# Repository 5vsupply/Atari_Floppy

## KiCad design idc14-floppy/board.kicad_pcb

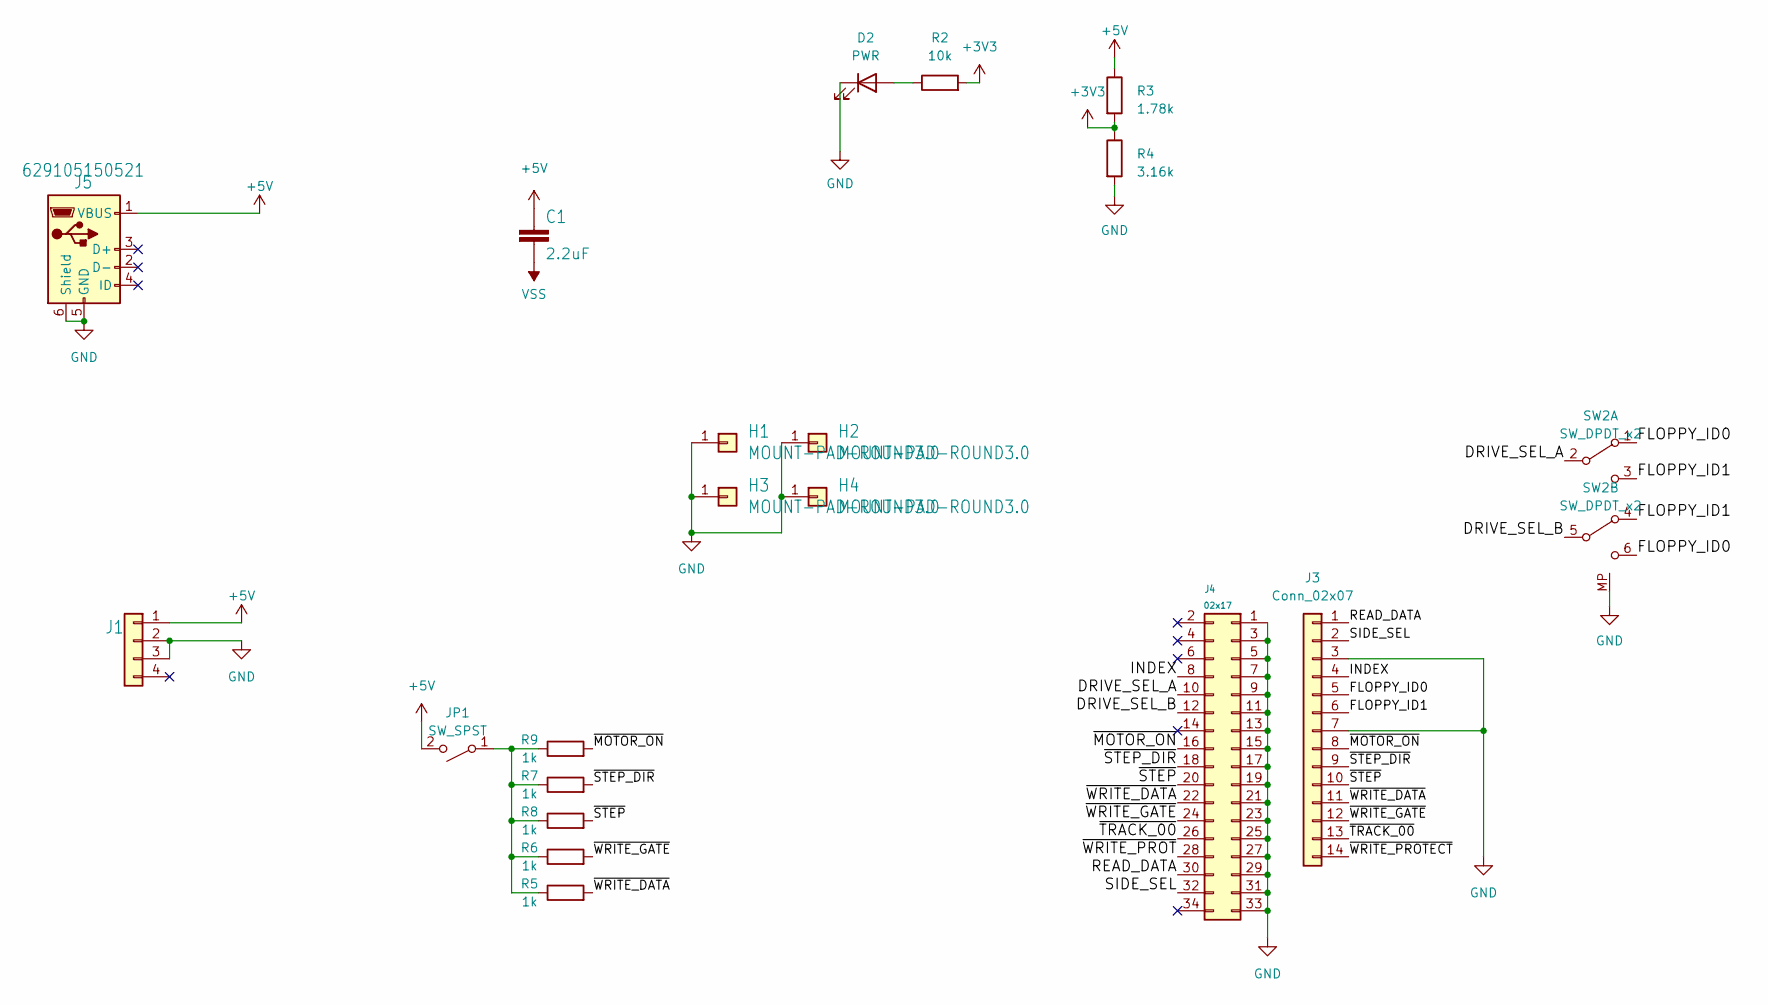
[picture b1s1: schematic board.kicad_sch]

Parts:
C1: 2.2uF; C_0805_2012Metric
D2: PWR; LED_0805_2012Metric
H1, H2, H3, H4: MOUNT-PAD-ROUND3.0; MountingHole_3.2mm_M3_Pad_Via
J1: 171826-4
J3: Conn_02x07; IDC-Header_2x07_P2.54mm_Horizontal
J4: 02x17; PinHeader_2x17_P2.54mm_Vertical
J5: 629105150521; USB_Micro-B_Wuerth_629105150521
JP1: SW_SPST
R2: 10k; R_0805_2012Metric
R3: 1.78k; R_0805_2012Metric
R4: 3.16k; R_0805_2012Metric
R5, R6, R7, R8, R9: 1k; R_0805_2012Metric
SW2: SW_DPDT_x2; SW_E-Switch_EG2219_DPDT_Angled

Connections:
+3V3: R2.2, R3.2, R4.1
+5V: C1.1, J1.1, J5.1 (VBUS), JP1.2 (B), R3.1
/DRIVE_SEL_A: J4.10, SW2.2 (B)
/DRIVE_SEL_B: J4.12, SW2.5 (B)
/FLOPPY_ID0: J3.5, SW2.1 (A), SW2.6 (C)
/FLOPPY_ID1: J3.6, SW2.3 (C), SW2.4 (A)
/INDEX: J3.4, J4.8
/READ_DATA: J3.1, J4.30
/SIDE_SEL: J3.2, J4.32
/~MOTOR_ON: J3.8, J4.16, R9.2
/~STEP_DIR: J3.9, J4.18, R7.2
/~STEP: J3.10, J4.20, R8.2
/~TRACK_00: J3.13, J4.26
/~WRITE_DATA: J3.11, J4.22, R5.2
/~WRITE_GATE: J3.12, J4.24, R6.2
/~WRITE_PROTECT: J3.14
/~WRITE_PROT: J4.28
GND: D2.1 (K), H1.1, H2.1, H3.1, H4.1, J1.2, J1.3, J3.3, J3.7, J4.1, J4.3, J4.5, J4.7, J4.9, J4.11, J4.13, J4.15, J4.17, J4.19, J4.21, J4.23, J4.25, J4.27, J4.29, J4.31, J4.33, J5.5 (GND), J5.6 (Shield), R4.2, SW2.MP
unnamed: D2.2 (A), R2.1
unnamed: JP1.1 (A), R5.1, R6.1, R7.1, R8.1, R9.1
VSS: C1.2

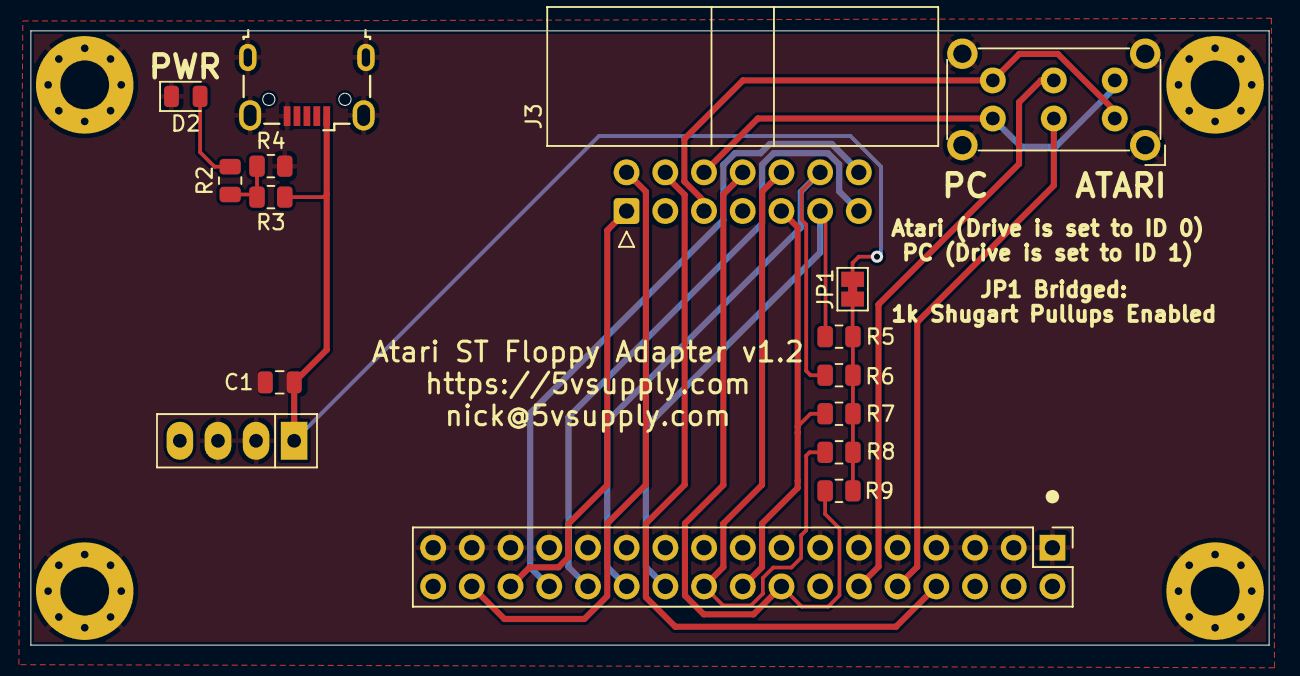
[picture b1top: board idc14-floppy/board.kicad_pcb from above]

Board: 2 copper layers, 81.3 x 40.3 mm, 20 parts (0 on the bottom side), 18 nets.

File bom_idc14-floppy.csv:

QUANTITY,DESCRIPTION,PART
1,Wurth 629105150521 Micro USB-B Connector,629105150521
1,34-pin 2.54mm Shrouded Through-Hole Vertical Connector,30334-6002HB
1,14-pin 2.54mm Shrouded Through-Hole Right-Angle Connector,SBH11-PBPC-D07-RA-BK
1,Right-Angle Through-Hole DPDT Switch,EG2219
1,3.3v 0603 LED,150060GS75000
1,10k 0.1w 0603 SMT Resistor,CRCW060310K0JNEBC
1,3.16k 0.1w 0603 SMT Resistor,CRCW06033K16FKEA
1,1.78k 0.1w 0603 SMT Resistor,CR0603-FX-1781ELF
1,2.2uF 6.3V 0603 SMT Capacitor,CL10A225KQ8NNNC
1,AMP 4-pin Right-Angle Male Connector,171826-4

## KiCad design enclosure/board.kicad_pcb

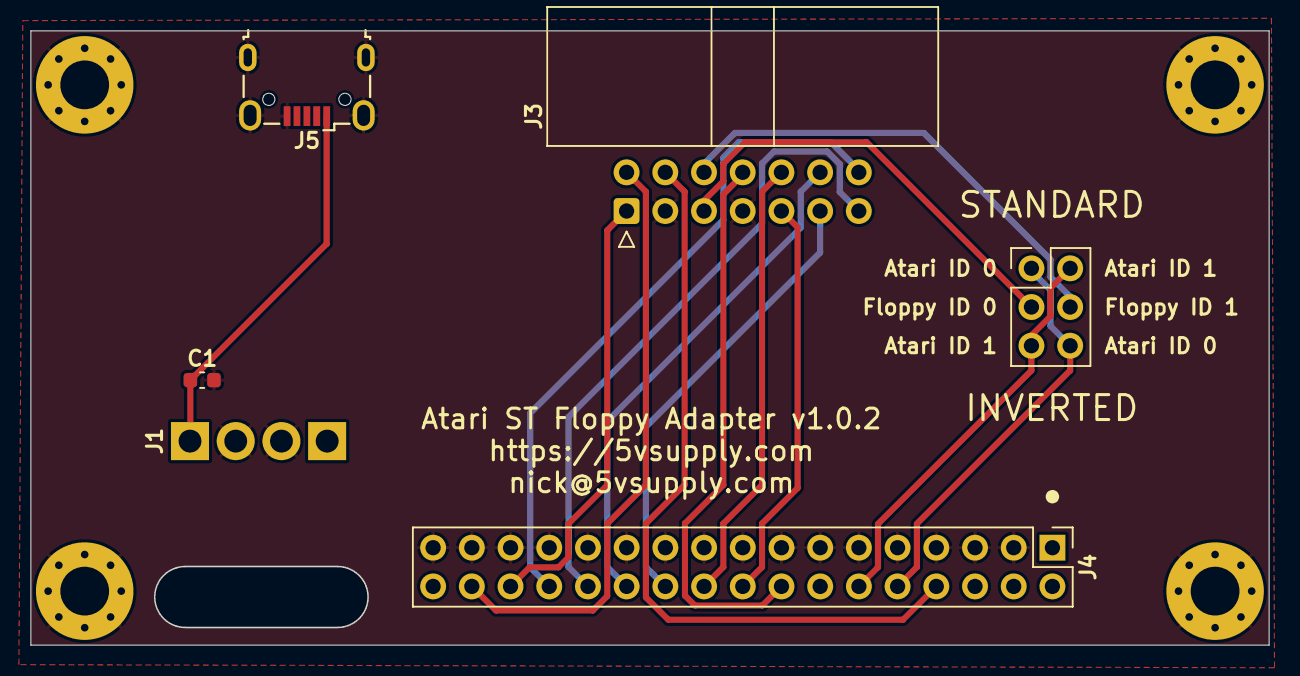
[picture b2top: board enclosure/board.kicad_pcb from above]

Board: 2 copper layers, 81.3 x 40.3 mm, 10 parts (0 on the bottom side), 16 nets.

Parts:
C1: 2.2uF; C_0603_1608Metric
H1, H2, H3, H4: MOUNT-PAD-ROUND3.0; MountingHole_3.2mm_M3_Pad_Via
J1: 61900411021; PinHeader_1x04_P2.54mm_Vertical
J3: 2x7; IDC-Header_2x07_P2.54mm_Horizontal
J4: 02x17; PinHeader_2x17_P2.54mm_Vertical
J5: 629105150521; USB_Micro-B_Wuerth_629105150521
SW1: SW_DPDT_x2; PinHeader_2x03_P2.54mm_Vertical

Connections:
/DRIVE_SEL_A: J4.10, SW1.1 (A), SW1.6 (C)
/DRIVE_SEL_B: J4.12, SW1.3 (C), SW1.4 (A)
/FLOPPY_ID0: J3.5, SW1.2 (B)
/FLOPPY_ID1: J3.6, SW1.5 (B)
/INDEX: J3.4, J4.8
/MOTOR_ON: J3.8, J4.16
/READ_DATA: J3.1, J4.30
/SIDE_SEL: J3.2, J4.32
/STEP: J3.10, J4.20
/STEP_DIR: J3.9, J4.18
/TRACK_00: J3.13, J4.26
/WRITE_DATA: J3.11, J4.22
/WRITE_GATE: J3.12, J4.24
/WRITE_PROT: J3.14, J4.28
GND: C1.2, H1.1, H2.1, H3.1, H4.1, J1.2, J1.3, J3.3, J3.7, J4.3, J4.5, J4.7, J4.9, J4.11, J4.13, J4.15, J4.17, J4.19, J4.21, J4.23, J4.25, J4.27, J4.29, J4.31, J4.33, J5.5 (GND), J5.6 (Shield)
VCC: C1.1, J1.1, J5.1 (VBUS)

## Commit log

2021-03-24 Initial Release
2021-03-30 Add BOM
2021-04-11 Fix cap value, thicker text, and minor layout tweaks
2021-05-09 initial v2 tweaks
2021-05-13 spacing tweaks
2021-05-13 add info to board
2021-05-30 reorganize, start enclosure
2021-06-21 footprint
2021-10-01 1.10 final
2021-10-01 v1.1.0 BOM
2022-04-30 1.2 test
